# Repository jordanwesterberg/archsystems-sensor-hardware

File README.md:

# archsystems-sensor-hardware
Created to measure the use patterns of income generating appliances powered by diesel engines in developing economies

These data generated by these sensors will help transition these appliances from being powered by diesel fuel to renewable energy.
The assembly can be used to log usage by measuring the RPM on the engine by counting the rotations of a magnet mounted to the appliance’s pulley wheel.
The housing head protects an (indepedently sourced) PCB board and reed switch that actively counts the magnet’s reps and stores the data in the Arch Pod (from Arch Systems) below it.
The information is transmitted to a cloud database via smartphone app and Bluetooth low energy.
The assembly was built around the existing Arch Systems Pod (https://archsys.io/) and designed to measure RPM accurately over many different use cases.
The armatures that connect the housing head and Pod cap can be easily adjusted with minimal hardware to fit the needs of many different height requirements and distances from the appliance’s pulley wheel.

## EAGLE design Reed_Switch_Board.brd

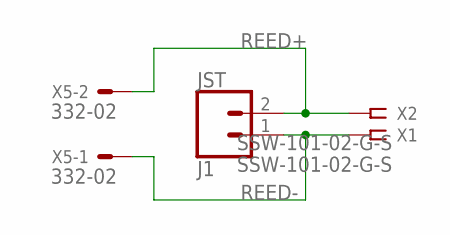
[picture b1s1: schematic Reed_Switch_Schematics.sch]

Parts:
J1: JST; JST-2-SMD
X1, X2: SSW-101-02-G-S
X5: 332-02

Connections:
REED+: J1.2 (1), X2.1, X5.2
REED-: J1.1 (2), X1.1, X5.1

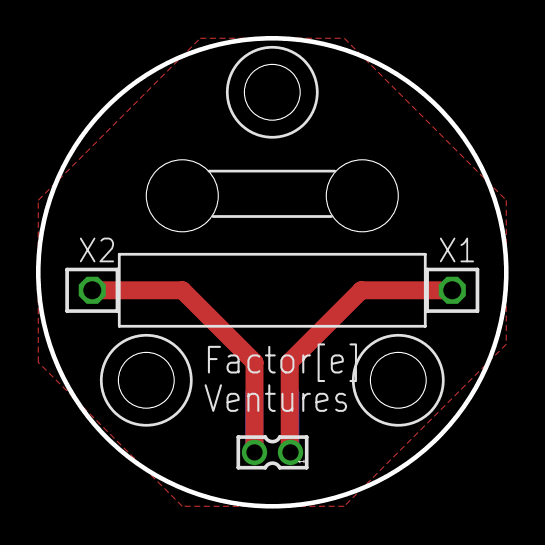
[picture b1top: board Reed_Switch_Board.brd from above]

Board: 2 copper layers, 26.0 x 26.0 mm, 4 parts (1 on the bottom side), 2 nets.

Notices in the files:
parts and their libraries:
SparkFun-Connectors: Licensing: Creative Commons ShareAlike 4.0 International - https://creativecommons.org/licenses/by-sa/4.0
